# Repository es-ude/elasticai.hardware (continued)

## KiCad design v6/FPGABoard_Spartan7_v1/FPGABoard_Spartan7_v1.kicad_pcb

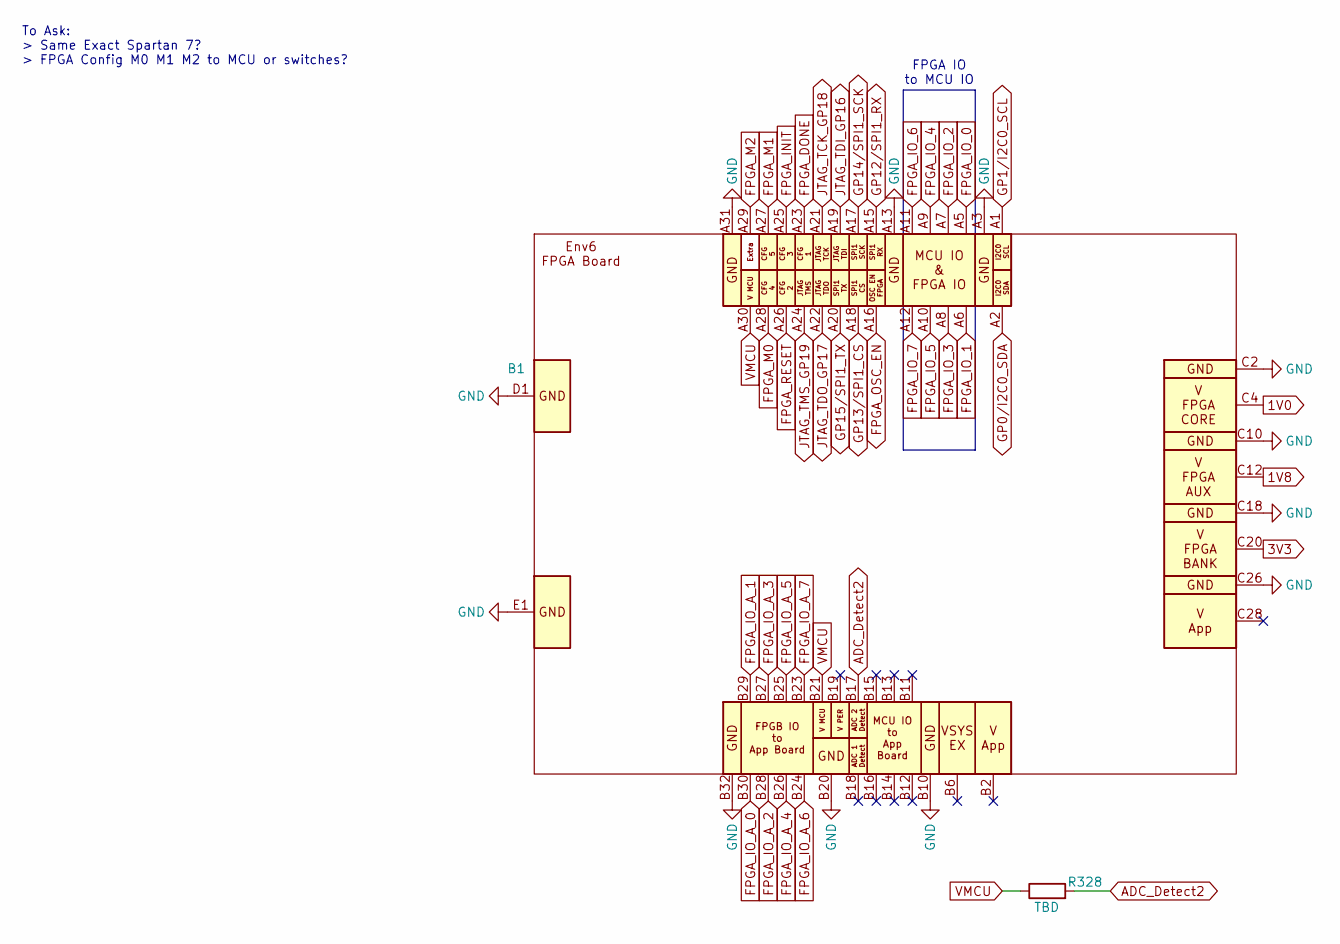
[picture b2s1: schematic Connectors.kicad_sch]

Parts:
B1: ExtensionBoard_ENv6
R328: TBD; R_0402_1005Metric

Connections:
1V0: B1.C3, B1.C4, B1.C5, B1.C6, B1.C7, B1.C8
1V8: B1.C11, B1.C12, B1.C13, B1.C14, B1.C15, B1.C16
3V3: B1.C19, B1.C20, B1.C21, B1.C22, B1.C23, B1.C24
ADC_Detect2: B1.B17, R328.2
FPGA_DONE: B1.A23; also elsewhere on the board
FPGA_INIT: B1.A25; also elsewhere on the board
FPGA_IO_0: B1.A5; also elsewhere on the board
FPGA_IO_1: B1.A6; also elsewhere on the board
FPGA_IO_2: B1.A7; also elsewhere on the board
FPGA_IO_3: B1.A8; also elsewhere on the board
FPGA_IO_4: B1.A9; also elsewhere on the board
FPGA_IO_5: B1.A10; also elsewhere on the board
FPGA_IO_6: B1.A11; also elsewhere on the board
FPGA_IO_7: B1.A12; also elsewhere on the board
FPGA_IO_A_0: B1.B30; also elsewhere on the board
FPGA_IO_A_1: B1.B29; also elsewhere on the board
FPGA_IO_A_2: B1.B28; also elsewhere on the board
FPGA_IO_A_3: B1.B27; also elsewhere on the board
FPGA_IO_A_4: B1.B26; also elsewhere on the board
FPGA_IO_A_5: B1.B25; also elsewhere on the board
FPGA_IO_A_6: B1.B24; also elsewhere on the board
FPGA_IO_A_7: B1.B23; also elsewhere on the board
FPGA_M0: B1.A28; also elsewhere on the board
FPGA_M1: B1.A27; also elsewhere on the board
FPGA_M2: B1.A29; also elsewhere on the board
FPGA_OSC_EN: B1.A16
FPGA_RESET: B1.A26; also elsewhere on the board
GND: B1.A3, B1.A4, B1.A13, B1.A14, B1.A31, B1.A32, B1.B9, B1.B10, B1.B20, B1.B22, B1.B31, B1.B32, B1.C1, B1.C2, B1.C9, B1.C10, B1.C17, B1.C18, B1.C25, B1.C26, B1.D1, B1.D2, B1.D3, B1.D4, B1.D5, B1.D6, B1.D7, B1.D8, B1.E1, B1.E2, B1.E3, B1.E4, B1.E5, B1.E6, B1.E7, B1.E8; also elsewhere on the board
GP0/I2C0_SDA: B1.A2
GP1/I2C0_SCL: B1.A1
GP12/SPI1_RX: B1.A15
GP13/SPI1_CS: B1.A18
GP14/SPI1_SCK: B1.A17
GP15/SPI1_TX: B1.A20
JTAG_TCK_GP18: B1.A21; also elsewhere on the board
JTAG_TDI_GP16: B1.A19; also elsewhere on the board
JTAG_TDO_GP17: B1.A22; also elsewhere on the board
JTAG_TMS_GP19: B1.A24; also elsewhere on the board
VMCU: B1.A30, B1.B21, R328.1

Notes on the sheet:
To Ask: > Same Exact Spartan 7? > FPGA Config M0 M1 M2 to MCU or switches?
FPGA IO to MCU IO

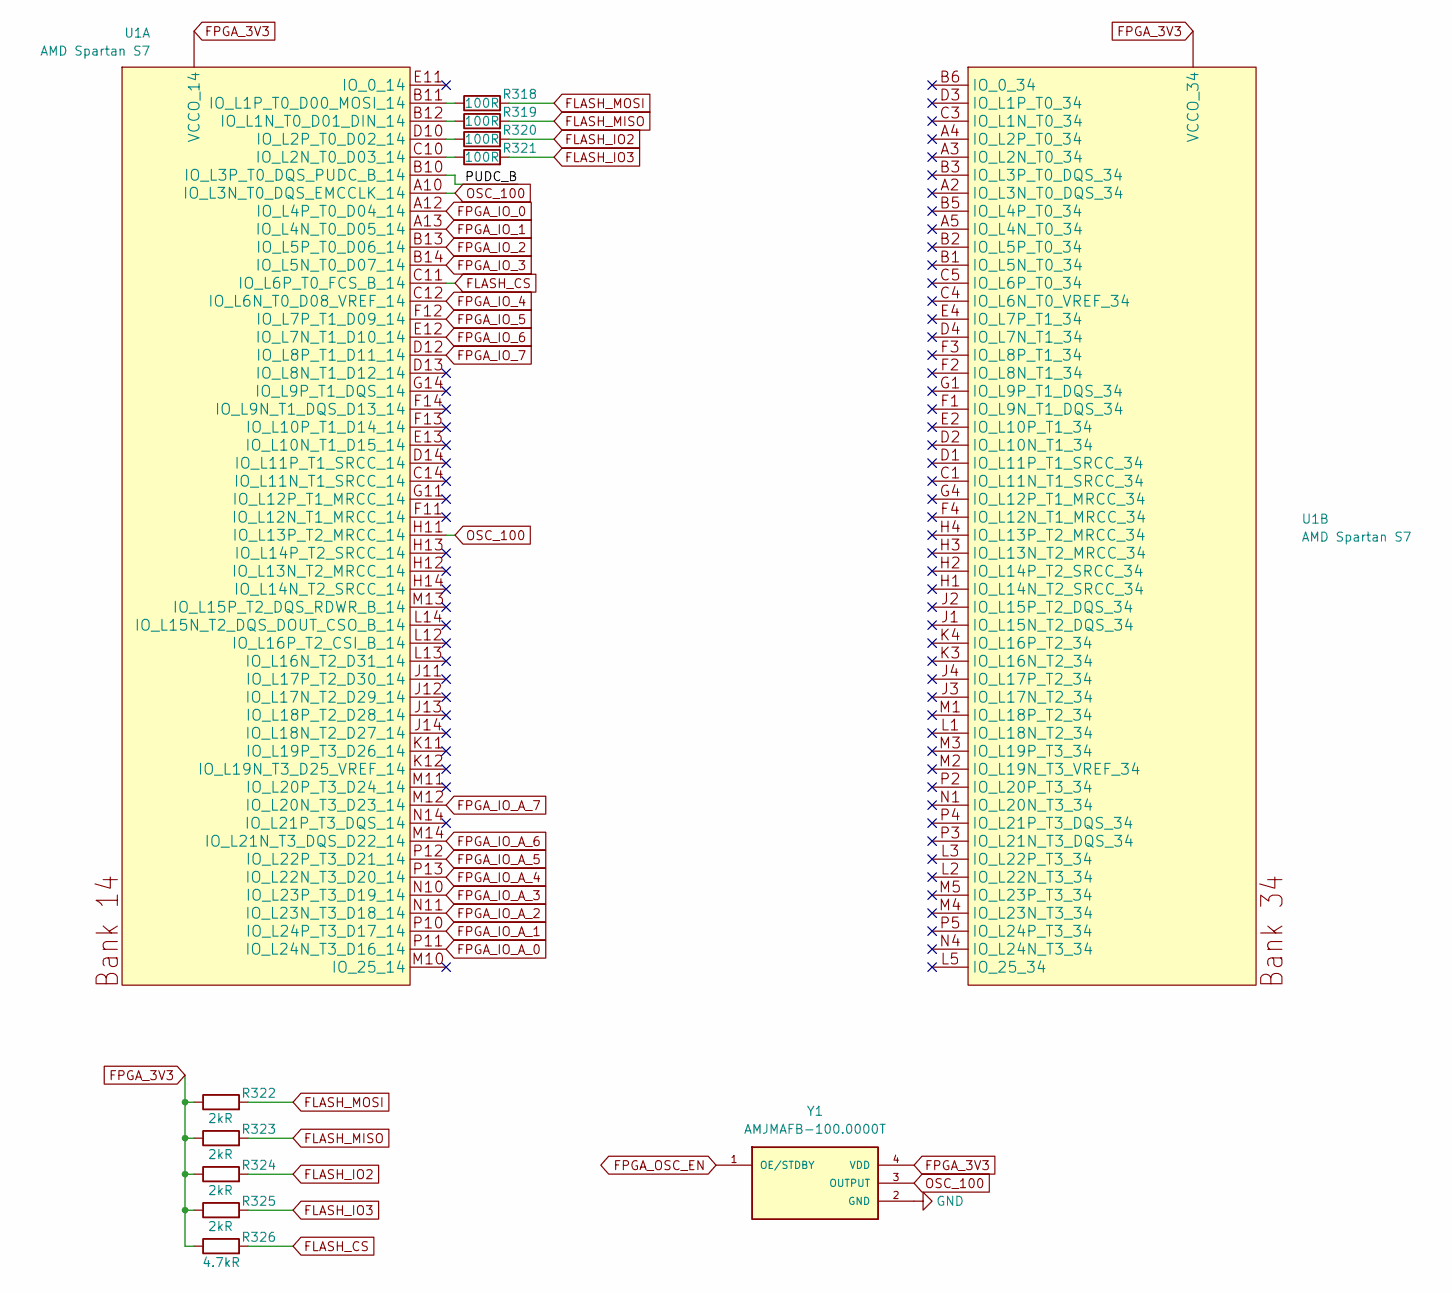
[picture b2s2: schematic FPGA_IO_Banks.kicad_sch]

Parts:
R318, R319, R320, R321: 100R; R_0402_1005Metric
R322, R323, R324, R325: 2kR; R_0402_1005Metric
R326: 4.7kR; R_0402_1005Metric
U1: AMD Spartan S7; BGA_FTGB196
Y1: AMJMAFB-100.0000T; XTAL_AMJMAFB-100.0000T; PARTREV 04/07/2021

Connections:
/FPGA_IO_Banks/PUDC_B: U1.B10 (IO_L3P_T0_DQS_PUDC_B_14)
FLASH_CS: R326.2, U1.C11 (IO_L6P_T0_FCS_B_14); also elsewhere on the board
FLASH_IO2: R320.2, R324.2; also elsewhere on the board
FLASH_IO3: R321.2, R325.2; also elsewhere on the board
FLASH_MISO: R319.2, R323.2; also elsewhere on the board
FLASH_MOSI: R318.2, R322.2; also elsewhere on the board
FPGA_3V3: R322.1, R323.1, R324.1, R325.1, R326.1, U1.G2 (VCCO_34), U1.G13 (VCCO_14), U1.K2 (VCCO_34), U1.K13 (VCCO_14), U1.N2 (VCCO_34), U1.N13 (VCCO_14), Y1.4 (VDD); also elsewhere on the board
FPGA_IO_0: U1.A12 (IO_L4P_T0_D04_14); also elsewhere on the board
FPGA_IO_1: U1.A13 (IO_L4N_T0_D05_14); also elsewhere on the board
FPGA_IO_2: U1.B13 (IO_L5P_T0_D06_14); also elsewhere on the board
FPGA_IO_3: U1.B14 (IO_L5N_T0_D07_14); also elsewhere on the board
FPGA_IO_4: U1.C12 (IO_L6N_T0_D08_VREF_14); also elsewhere on the board
FPGA_IO_5: U1.F12 (IO_L7P_T1_D09_14); also elsewhere on the board
FPGA_IO_6: U1.E12 (IO_L7N_T1_D10_14); also elsewhere on the board
FPGA_IO_7: U1.D12 (IO_L8P_T1_D11_14); also elsewhere on the board
FPGA_IO_A_0: U1.P11 (IO_L24N_T3_D16_14); also elsewhere on the board
FPGA_IO_A_1: U1.P10 (IO_L24P_T3_D17_14); also elsewhere on the board
FPGA_IO_A_2: U1.N11 (IO_L23N_T3_D18_14); also elsewhere on the board
FPGA_IO_A_3: U1.N10 (IO_L23P_T3_D19_14); also elsewhere on the board
FPGA_IO_A_4: U1.P13 (IO_L22N_T3_D20_14); also elsewhere on the board
FPGA_IO_A_5: U1.P12 (IO_L22P_T3_D21_14); also elsewhere on the board
FPGA_IO_A_6: U1.M14 (IO_L21N_T3_DQS_D22_14); also elsewhere on the board
FPGA_IO_A_7: U1.M12 (IO_L20N_T3_D23_14); also elsewhere on the board
unnamed: R319.1, U1.B12 (IO_L1N_T0_D01_DIN_14)
unnamed: R318.1, U1.B11 (IO_L1P_T0_D00_MOSI_14)
unnamed: R321.1, U1.C10 (IO_L2N_T0_D03_14)
unnamed: R320.1, U1.D10 (IO_L2P_T0_D02_14)
OSC_100: U1.A10 (IO_L3N_T0_DQS_EMCCLK_14), U1.H11 (IO_L13P_T2_MRCC_14), Y1.3 (OUTPUT)

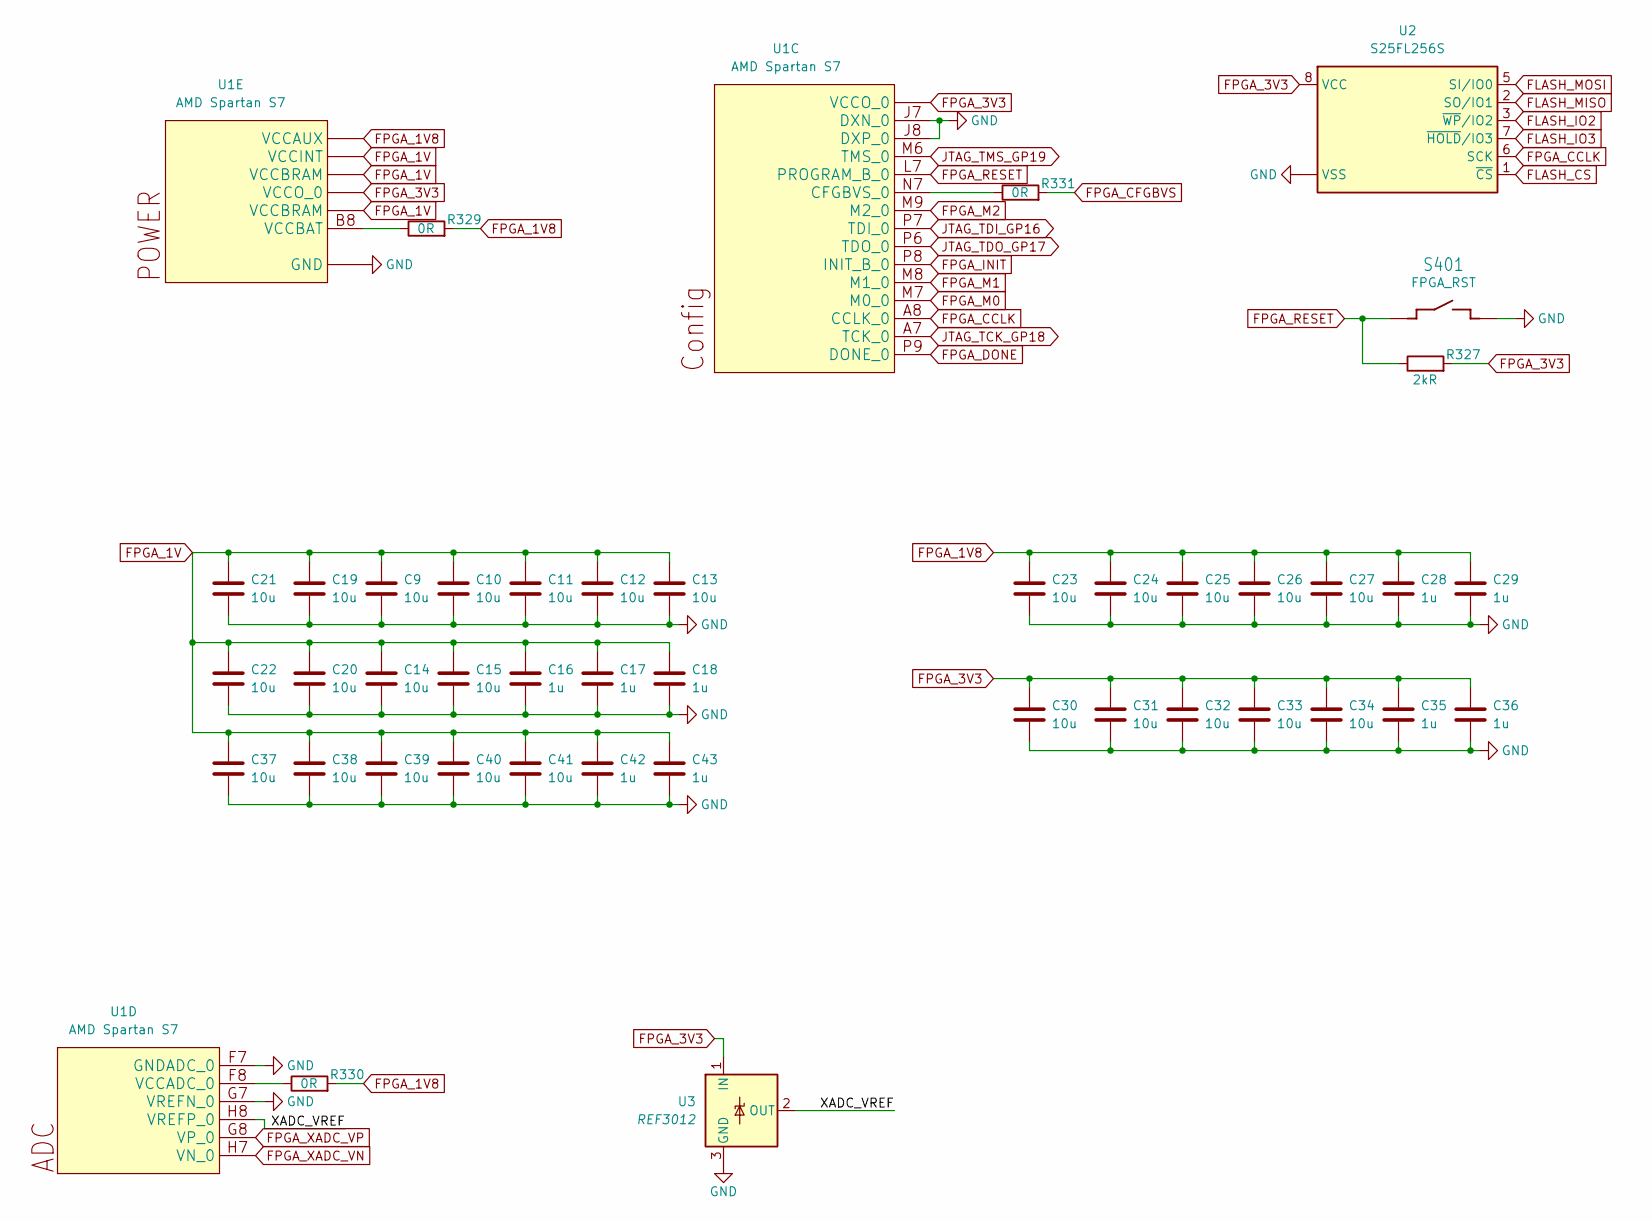
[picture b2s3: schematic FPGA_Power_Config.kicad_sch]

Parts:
C9, C10, C11, C12, C13, C14, C15, C19, C20, C21, C22, C23, C24, C25, C26, C27, C30, C31, C32, C33, C34, C37, C38, C39, C40, C41: 10u; C_0402_1005Metric
C16, C17, C18, C28, C29, C35, C36, C42, C43: 1u; C_0402_1005Metric
R327: 2kR; R_0402_1005Metric
R329, R330, R331: 0R; R_0402_1005Metric
S401: FPGA_RST; TACTILE-SWITCH
U1: AMD Spartan S7; BGA_FTGB196
U2: S25FL256S; WSON-8_EP_8x6_Pitch1.27mm
U3: REF3012; SOT-23

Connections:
/FPGA_Power_Config/XADC_VREF: U1.H8 (VREFP_0), U3.2 (OUT)
FLASH_CS: U2.1 (~CS); also elsewhere on the board
FLASH_IO2: U2.3 (~WP/IO2); also elsewhere on the board
FLASH_IO3: U2.7 (~HOLD/IO3); also elsewhere on the board
FLASH_MISO: U2.2 (SO/IO1); also elsewhere on the board
FLASH_MOSI: U2.5 (SI/IO0); also elsewhere on the board
FPGA_1V: C9.2, C10.2, C11.2, C12.2, C13.2, C14.2, C15.2, C16.2, C17.2, C18.2, C19.2, C20.2, C21.2, C22.2, C37.2, C38.2, C39.2, C40.2, C41.2, C42.2, C43.2, U1.D6 (VCCINT), U1.D8 (VCCINT), U1.E5 (VCCBRAM), U1.E7 (VCCINT), U1.E9 (VCCINT), U1.F6 (VCCINT), U1.G5 (VCCBRAM), U1.G9 (VCCINT), U1.H6 (VCCINT), U1.J5 (VCCBRAM), U1.J9 (VCCINT), U1.K6 (VCCINT), U1.K8 (VCCINT)
FPGA_1V8: C23.2, C24.2, C25.2, C26.2, C27.2, C28.2, C29.2, R329.2, R330.2, U1.F10 (VCCAUX), U1.H10 (VCCAUX), U1.K10 (VCCAUX), U1.L9 (VCCAUX)
FPGA_3V3: C30.2, C31.2, C32.2, C33.2, C34.2, C35.2, C36.2, R327.2, U1.N6 (VCCO_0), U1.N8 (VCCO_0), U2.8 (VCC), U3.1 (IN); also elsewhere on the board
FPGA_CCLK: U1.A8 (CCLK_0), U2.6 (SCK)
FPGA_CFGBVS: R331.2
FPGA_DONE: U1.P9 (DONE_0); also elsewhere on the board
FPGA_INIT: U1.P8 (INIT_B_0); also elsewhere on the board
FPGA_M0: U1.M7 (M0_0); also elsewhere on the board
FPGA_M1: U1.M8 (M1_0); also elsewhere on the board
FPGA_M2: U1.M9 (M2_0); also elsewhere on the board
FPGA_RESET: R327.1, S401.1, S401.2 (1), U1.L7 (PROGRAM_B_0); also elsewhere on the board
FPGA_XADC_VN: U1.H7 (VN_0)
FPGA_XADC_VP: U1.G8 (VP_0)
GND: C9.1, C10.1, C11.1, C12.1, C13.1, C14.1, C15.1, C16.1, C17.1, C18.1, C19.1, C20.1, C21.1, C22.1, C23.1, C24.1, C25.1, C26.1, C27.1, C28.1, C29.1, C30.1, C31.1, C32.1, C33.1, C34.1, C35.1, C36.1, C37.1, C38.1, C39.1, C40.1, C41.1, C42.1, C43.1, S401.3 (2), S401.4 (2), U1.A1 (GND), U1.A6 (GND), U1.A9 (GND), U1.A11 (GND), U1.A14 (GND), U1.B4 (GND), U1.B7 (GND), U1.B9 (GND), U1.C2 (GND), U1.C6 (GND), U1.C7 (GND), U1.C8 (GND), U1.C9 (GND), U1.C13 (GND), U1.D5 (GND), U1.D7 (GND), U1.D9 (GND), U1.D11 (GND), U1.E1 (GND), U1.E3 (GND), U1.E6 (GND), U1.E8 (GND), U1.E10 (GND), U1.E14 (GND), U1.F5 (GND), U1.F7 (GNDADC_0), U1.F9 (GND), U1.G3 (GND), U1.G6 (GND), U1.G7 (VREFN_0), U1.G10 (GND), U1.G12 (GND), U1.H5 (GND), U1.H9 (GND), U1.J6 (GND), U1.J7 (DXN_0), U1.J8 (DXP_0), U1.J10 (GND), U1.K1 (GND), U1.K5 (GND), U1.K7 (GND), U1.K9 (GND), U1.K14 (GND), U1.L4 (GND), U1.L6 (GND), U1.L8 (GND), U1.L10 (GND), U1.L11 (GND), U1.N3 (GND), U1.N5 (GND), U1.N9 (GND), U1.N12 (GND), U1.P1 (GND), U1.P14 (GND), U2.4 (VSS), U2.9 (VSS), U3.3 (GND); also elsewhere on the board
JTAG_TCK_GP18: U1.A7 (TCK_0); also elsewhere on the board
JTAG_TDI_GP16: U1.P7 (TDI_0); also elsewhere on the board
JTAG_TDO_GP17: U1.P6 (TDO_0); also elsewhere on the board
JTAG_TMS_GP19: U1.M6 (TMS_0); also elsewhere on the board
unnamed: R331.1, U1.N7 (CFGBVS_0)
unnamed: R330.1, U1.F8 (VCCADC_0)
unnamed: R329.1, U1.B8 (VCCBAT)

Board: 2 copper layers, 54 parts (0 on the bottom side), 50 nets, no tracks yet.

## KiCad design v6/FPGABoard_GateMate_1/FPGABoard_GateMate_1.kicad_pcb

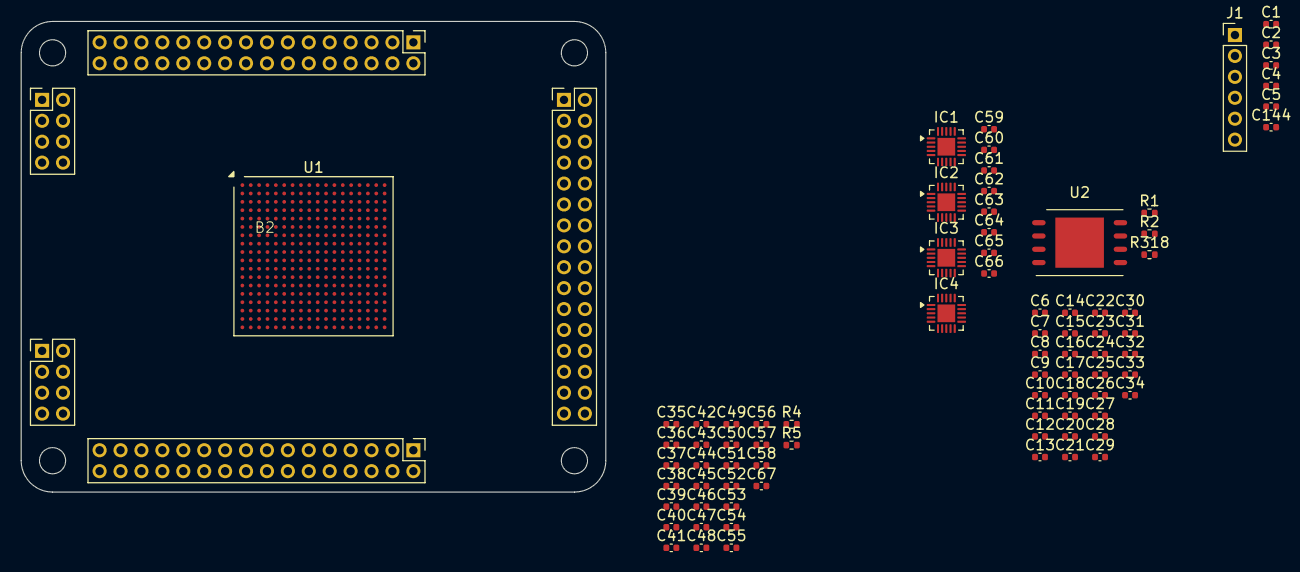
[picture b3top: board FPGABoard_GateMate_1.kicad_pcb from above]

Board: 2 copper layers, 55.9 x 45.0 mm, 81 parts (0 on the bottom side), 82 nets, no tracks yet.

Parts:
B2: ExtensionBoard_ENv6
C1, C3, C5, C6, C8, C9, C10, C12, C13, C15, C16, C18, C19, C20, C21, C23, C24, C25, C27, C28, C29, C31, C32, C33, C34, C35, C36, C38, C39, C42, C43, C44, C45, C48, C49, C50, C51, C54, C55, C56, C57, C59, C60, C61, C62, C63, C64, C65, C66, C67, C144: 0.1u; C_0402_1005Metric
C2, C4, C7, C11, C14, C17, C22, C26, C30, C37, C40, C41, C46, C47, C52, C53, C58: 2.2u; C_0402_1005Metric
IC1, IC2, IC3, IC4: TXB0108RUKR; WQFN-20-1EP_3x3mm_P0.4mm_EP1.7x1.7mm
J1: Conn_01x06_Pin; PinHeader_1x06_P2.00mm_Vertical
R1, R318: 0R; R_0402_1005Metric
R2: 200R; R_0402_1005Metric
R4, R5: 5k1; R_0402_1005Metric
U1: CCGM1A1; BGA-324_15x15mm_Layout18x18_P0.8mm
U2: W25Q16JVUXIQ; WSON-8_EP_8x6_Pitch1.27mm

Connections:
/1V0: B2.C3, B2.C4, B2.C5, B2.C6, B2.C7, B2.C8
/2V5: B2.C11, B2.C12, B2.C13, B2.C14, B2.C15, B2.C16, C59.2, C62.2, C63.2, C64.2, IC1.8 (OE), IC1.20 (VCCA), IC2.8 (OE), IC2.20 (VCCA), IC3.8 (OE), IC3.20 (VCCA), IC4.8 (OE), IC4.20 (VCCA)
/Connectors/V4: B2.B1, B2.B2, B2.B3, B2.B4, B2.C27, B2.C28, B2.C29, B2.C30, B2.C31, B2.C32
/Connectors/V_App_Board: B2.B21, B2.B24, C60.2, IC4.17 (VCCB)
/FPGA_Config/SER_CLK_N: J1.1, U1.T13 (SER_CLK_N)
/FPGA_Config/SER_CLK_P: J1.2, U1.T12 (SER_CLK)
/FPGA_Config/SER_RX_N: J1.5, U1.V11 (SER_RX_N)
/FPGA_Config/SER_RX_P: J1.6, U1.U11 (SER_RX_P)
/FPGA_Config/SER_TX_N: J1.4, U1.V13 (SER_TX_N)
/FPGA_Config/SER_TX_P: J1.3, U1.U13 (SER_TX_P)
/FPGA_Config/VDD_IO: C1.2, C2.2, C3.2, C4.2, C5.2, C144.2, U1.N5 (VDD_WA), U1.P3 (VDD_WA), U1.P5 (VDD_WA), U1.T1 (VDD_WA), U1.T14 (VDD_CLK), U1.U3 (VDD_WA), U2.8 (VCC)
/FPGA_IO_Banks/VDD_IO: C35.2, C36.2, C37.2, C38.2, C39.2, C40.2, C41.2, C42.2, C43.2, C44.2, C45.2, C46.2, C47.2, C48.2, C49.2, C50.2, C51.2, C52.2, C53.2, C54.2, C55.2, C56.2, C57.2, C58.2, C67.2, R4.2, R5.1, U1.A2 (VDD_WC), U1.A5 (VDD_NA), U1.A16 (VDD_EB), U1.B7 (VDD_NA), U1.B10 (VDD_NB), U1.B13 (VDD_NB), U1.B18 (VDD_EB), U1.C2 (VDD_WC), U1.D5 (VDD_WC), U1.E6 (VDD_NA), U1.E8 (VDD_NA), U1.E10 (VDD_NB), U1.E12 (VDD_NB), U1.E14 (VDD_EB), U1.E17 (VDD_EB), U1.F2 (VDD_WC), U1.F5 (VDD_WC), U1.F7 (VDD_NA), U1.F11 (VDD_NB), U1.F13 (VDD_EB), U1.G14 (VDD_EA), U1.H5 (VDD_WB), U1.H17 (VDD_EA), U1.J2 (VDD_WB), U1.J14 (VDD_EA), U1.K5 (VDD_WB), U1.L14 (VDD_EA), U1.L17 (VDD_EA), U1.M2 (VDD_WB), U1.M5 (VDD_WB), U1.N11 (VDD_SB), U1.N13 (VDD_SB), U1.N18 (VDD_SB), U1.P6 (VDD_SA), U1.P8 (VDD_SA), U1.P10 (VDD_SA), U1.R15 (VDD_SB), U1.T18 (VDD_SB), U1.U6 (VDD_SA), U1.U9 (VDD_SA)
/FPGA_Power/VDD_CORE: C6.2, C7.2, C8.2, C9.2, C10.2, C11.2, C12.2, C13.2, C14.2, C15.2, C16.2, C17.2, C18.2, C19.2, C20.2, C21.2, C22.2, C23.2, C24.2, C25.2, C26.2, C27.2, C28.2, C29.2, C30.2, C31.2, C32.2, C33.2, C34.2, U1.F9 (VDD), U1.G6 (VDD), U1.G8 (VDD), U1.G10 (VDD), U1.G12 (VDD), U1.H7 (VDD), U1.H9 (VDD), U1.H11 (VDD), U1.H13 (VDD), U1.J6 (VDD), U1.J8 (VDD), U1.J10 (VDD), U1.J12 (VDD), U1.K7 (VDD), U1.K9 (VDD), U1.K11 (VDD), U1.K13 (VDD), U1.L6 (VDD), U1.L8 (VDD), U1.L10 (VDD), U1.L12 (VDD), U1.M7 (VDD), U1.M9 (VDD), U1.M11 (VDD), U1.M13 (VDD), U1.N6 (VDD), U1.N8 (VDD), U1.N10 (VDD), U1.P16 (VDD_PLL), U1.T16 (VDD_SER_PLL), U1.U12 (VDD_SER), U1.V17 (VDD_SER)
A_CFG_DONE: IC1.2 (A3), U1.K1 (IO_WB_A5)
A_CFG_Extra: IC1.19 (A1), U1.L1 (IO_WB_A3)
A_CFG_FAILED_N: IC1.1 (A2), U1.L2 (IO_WB_B3)
A_FPGA_RST: IC2.19 (A1), U1.G1 (IO_WC_A0)
A_GP0/I2C0_SDA: IC2.7 (A8), R5.2, U1.E2 (IO_WC_B3)
A_GP1/I2C0_SCL: IC2.6 (A7), R4.1, U1.E1 (IO_WC_A3)
A_GP12/SPI1_RX: IC2.4 (A5), R318.1
A_GP13/SPI1_CS: IC2.3 (A4), U1.N3 (IO_WA_A8/~SPI_CS), U2.1 (~CS)
A_GP14/SPI1_SCK: IC2.2 (A3), U1.N4 (IO_WA_B8/SPI_CLK), U2.6 (SCK)
A_GP15/SPI1_TX: IC2.1 (A2), R1.2
A_MCU-FPGA_EN_OSC: IC2.5 (A6), U1.G2 (IO_WC_B0)
A_POR_EN: IC1.3 (A4), U1.K2 (IO_WB_B5)
CFG_DONE: B2.A25, IC1.15 (B3), U1.V3 (IO_WA_B2/CFG_DONE)
CFG_Extra: B2.A27, IC1.18 (B1)
CFG_FAILED_N: B2.A28, IC1.16 (B2), U1.V2 (IO_WA_A2/~CFG_FAILED)
FPGA-MCU_GP3: IC3.7 (A8), U1.B2 (IO_WC_B8)
FPGA-MCU_GP4: IC3.6 (A7), U1.B1 (IO_WC_A8)
FPGA-MCU_GP5: IC3.5 (A6), U1.C4 (IO_WC_B7)
FPGA-MCU_GP6: IC3.4 (A5), U1.C3 (IO_WC_A7)
FPGA-MCU_GP7: IC3.3 (A4), U1.D4 (IO_WC_B6)
FPGA-MCU_GP8: IC3.2 (A3), U1.D3 (IO_WC_A6)
FPGA-MCU_GP9: IC3.1 (A2), U1.D2 (IO_WC_B5)
FPGA-MCU_GP10: IC3.19 (A1), U1.D1 (IO_WC_A5)
FPGA_AB_A1: IC4.19 (A1), U1.M18 (IO_SB_B3)
FPGA_AB_A2: IC4.1 (A2), U1.M17 (IO_SB_A3)
FPGA_AB_A3: IC4.2 (A3), U1.P18 (IO_SB_B2)
FPGA_AB_A4: IC4.3 (A4), U1.P17 (IO_SB_A2)
FPGA_AB_A5: IC4.4 (A5), U1.R18 (IO_SB_B1)
FPGA_AB_A6: IC4.5 (A6), U1.R17 (IO_SB_A1)
FPGA_AB_A7: IC4.6 (A7), U1.U18 (IO_SB_B0)
FPGA_AB_A8: IC4.7 (A8), U1.U17 (IO_SB_A0)
FPGA_AB_B1: B2.B26, IC4.18 (B1)
FPGA_AB_B2: B2.B23, IC4.16 (B2)
FPGA_AB_B3: B2.B28, IC4.15 (B3)
FPGA_AB_B4: B2.B25, IC4.14 (B4)
FPGA_AB_B5: B2.B30, IC4.13 (B5)
FPGA_AB_B6: B2.B27, IC4.12 (B6)
FPGA_AB_B7: B2.B31, B2.B32, IC4.11 (B7)
FPGA_AB_B8: B2.B29, IC4.10 (B8)
FPGA_RST: B2.A23, IC2.18 (B1), U1.T15 (~RESET)
GND: B2.A3, B2.A4, B2.A13, B2.A14, B2.A31, B2.A32, B2.B9, B2.B10, B2.C1, B2.C2, B2.C9, B2.C10, B2.C17, B2.C18, B2.C25, B2.C26, B2.D1, B2.D2, B2.D3, B2.D4, B2.D5, B2.D6, B2.D7, B2.D8, B2.E1, B2.E2, B2.E3, B2.E4, B2.E5, B2.E6, B2.E7, B2.E8, C1.1, C2.1, C3.1, C4.1, C5.1, C6.1, C7.1, C8.1, C9.1, C10.1, C11.1, C12.1, C13.1, C14.1, C15.1, C16.1, C17.1, C18.1, C19.1, C20.1, C21.1, C22.1, C23.1, C24.1, C25.1, C26.1, C27.1, C28.1, C29.1, C30.1, C31.1, C32.1, C33.1, C34.1, C35.1, C36.1, C37.1, C38.1, C39.1, C40.1, C41.1, C42.1, C43.1, C44.1, C45.1, C46.1, C47.1, C48.1, C49.1, C50.1, C51.1, C52.1, C53.1, C54.1, C55.1, C56.1, C57.1, C58.1, C59.1, C60.1, C61.1, C62.1, C63.1, C64.1, C65.1, C66.1, C67.1, C144.1, IC1.9 (GND), IC1.21 (GND), IC2.9 (GND), IC2.21 (GND), IC3.9 (GND), IC3.21 (GND), IC4.9 (GND), IC4.21 (GND), R2.1, U1.A1 (GND), U1.A7 (GND), U1.A10 (GND), U1.A13 (GND), U1.A18 (GND), U1.B16 (GND), U1.C1 (GND), U1.E5 (GND), U1.E7 (GND), U1.E9 (GND), U1.E11 (GND), U1.E13 (GND), U1.E18 (GND), U1.F1 (GND), U1.F6 (GND), U1.F8 (GND), U1.F10 (GND), U1.F12 (GND), U1.F14 (GND), U1.G5 (GND), U1.G7 (GND), U1.G9 (GND), U1.G11 (GND), U1.G13 (GND), U1.H6 (GND), U1.H8 (GND), U1.H10 (GND), U1.H12 (GND), U1.H14 (GND), U1.H18 (GND), U1.J1 (GND), U1.J5 (GND), U1.J7 (GND), U1.J9 (GND), U1.J11 (GND), U1.J13 (GND), U1.K6 (GND), U1.K8 (GND), U1.K10 (GND), U1.K12 (GND), U1.K14 (GND), U1.L5 (GND), U1.L7 (GND), U1.L9 (GND), U1.L11 (GND), U1.L13 (GND), U1.L18 (GND), U1.M1 (GND), U1.M6 (GND), U1.M8 (GND), U1.M10 (GND), U1.M12 (GND), U1.M16 (GND), U1.N7 (GND), U1.N9 (GND), U1.N12 (GND), U1.N17 (GND), U1.P4 (GND), U1.P7 (GND), U1.P9 (GND), U1.R12 (GND), U1.R16 (GND), U1.T4 (GND), U1.T11 (GND), U1.T17 (GND), U1.U14 (GND), U1.U15 (GND), U1.U16 (GND), U1.V1 (GND), U1.V6 (GND), U1.V9 (GND), U1.V14 (GND), U1.V16 (GND), U1.V18 (GND), U2.4 (VSS), U2.9 (VSS)
GP0/I2C0_SDA: B2.A2, IC2.10 (B8)
GP1/I2C0_SCL: B2.A1, IC2.11 (B7)
GP12/SPI1_RX: B2.A15, IC2.13 (B5)
GP13/SPI1_CS: B2.A18, IC2.14 (B4)
GP14/SPI1_SCK: B2.A17, IC2.15 (B3)
GP15/SPI1_TX: B2.A20, IC2.16 (B2)
JTAG_TCK_GP18: B2.A21, IC1.12 (B6), U1.R3 (JTAG_TCK/IO_WA_A5)
JTAG_TDI_GP16: B2.A19, IC1.10 (B8), U1.T2 (JTAG_TDI/IO_WA_A4)
JTAG_TDO_GP17: B2.A22, IC1.11 (B7), U1.U2 (JTAG_TDO/IO_WA_B3)
JTAG_TMS_GP19: B2.A24, IC1.13 (B5), U1.T3 (JTAG_TMS/IO_WA_B4)
MCU-FPGA_EN_OSC: B2.A16, IC2.12 (B6)
unnamed: B2.B20, B2.B22
unnamed: R2.2, U1.V12 (SER_RTERM)
unnamed: U1.R1 (IO_WA_A6/SPI_D3), U2.7 (~HOLD/IO3)
unnamed: R318.2, U1.P1 (IO_WA_A7/SPI_D1), U2.2 (SO/IO1)
unnamed: U1.R2 (IO_WA_B6/SPI_D2), U2.3 (~WP/IO2)
unnamed: R1.1, U1.P2 (IO_WA_B7/SPI_D0), U2.5 (SI/IO0)
POR_EN: B2.A26, IC1.14 (B4), U1.U1 (POR_EN/IO_WA_A3)
Unused_GP3: B2.A6, IC3.10 (B8)
Unused_GP4: B2.A5, IC3.11 (B7)
Unused_GP5: B2.A8, IC3.12 (B6)
Unused_GP6: B2.A7, IC3.13 (B5)
Unused_GP7: B2.A10, IC3.14 (B4)
Unused_GP8: B2.A9, IC3.15 (B3)
Unused_GP9: B2.A12, IC3.16 (B2)
Unused_GP10: B2.A11, IC3.18 (B1)
VDDD_MCU: B2.A29, C61.2, C65.2, C66.2, IC1.17 (VCCB), IC2.17 (VCCB), IC3.17 (VCCB)
VSYS_EX: B2.B5, B2.B6, B2.B7, B2.B8
